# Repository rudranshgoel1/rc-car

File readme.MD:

# Wireless RC Car

### Why did I make it?
bcz i need more hardware projects in my portfolio and also because it seemed like a fun hardware project which was kinda beginner friendly.

### What was the hardest part about this ?
schematic and choosing the pcb art. i really did wake up the creative side of me

Features:

- 4 Arrow Keys for controlling the car
- Arduino Nano for the Main MCU
- L298N Motor Driver
- DC Motors + Wheels
- Custom PCB Art (really cool)
- Custom case

### Fully Built Images

### Working Video

### Schematic

### PCB 

### Case

### 3D view of all parts 

link to full 3d thing-
https://cad.onshape.com/documents/55362c062752c5dd0b9c506b/w/202d1c84392a58531153413c/e/98ba119ae289950db80c791d?renderMode=0&uiState=6a291872275c9443df0429f0

A special thanks to Anay and Shadow who are helping me to make my projects better. Love them so much!

## BOM

[BOM](BOM.csv)

|Name                           |Purpose                            |Quantity|Total Cost (USD)|Link                                        |Distributor    |
|-------------------------------|-----------------------------------|--------|----------------|--------------------------------------------|---------------|
|Arduino Nano                   |Arduino Nano as the MCU            |2       |7.6             |https://www.amazon.in/gp/product/B077TJ8FCF/|Amazon         |
|NRF24L01 Transceiver Module    |Tranceiver module                  |1       |2.5             |https://www.amazon.in/gp/product/B073Q2W112/|Amazon         |
|NRF24L01 Transmitter Module    |Transmitter module                 |1       |2.8             |https://www.amazon.in/gp/product/B0H425R413/|Amazon         |
|Switches for Transmitter       |Switches for controlling the car   |4       |0               |SELF SOURCED                                |SELF SOURCED   |
|Keycaps for the swiches        |Keycaps of the switches            |4       |0               |SELF SOURCED                                |SELF SOURCED   |
|100nF Capacitor                |100nF Capacitor                    |1       |1.3             |https://www.amazon.in/gp/product/B0FCFYSP35/|Amazon         |
|10uF Capacitor                 |10uF Capacitor                     |1       |1.6             |https://www.amazon.in/gp/product/B0GKVJ5FXC/|Amazon         |
|PCB of Transmitter AND Receiver|Main PCBs                          |5 + 5   |16.84           |https://jlcpcb.com/                         |JLPCB          |
|L298N Motor Driver             |Motor which controls the wheels    |1       |2.1             |https://www.amazon.in/gp/product/B00N4KWYDE/|Amazon         |
|DC Motors + Wheels             |DC Motors + Wheels for the car     |1       |4.2             |https://www.amazon.in/gp/product/B07Q22QS3R/|Amazon         |
|Case                           |Shipping - Case for the transmitter|1       |5               |                                            |Printing Legion|
|                               |                                   |        |                |                                            |               |
|                               |                                   |        |43.94           |                                            |               |

Final Price comes out to be 4,185 INR ($43.94)

## Shipping
Amazon = ~$2
Printing Legion = ~$5

Total Shipping = $7

## Total Pricing
The total price comes out to be 4,850 INR ($50.94) [ SHIPPING INCLUDED ]
Total Shipping = $7

The pricing might slightly vary due to flash sales, and dollar market trends.

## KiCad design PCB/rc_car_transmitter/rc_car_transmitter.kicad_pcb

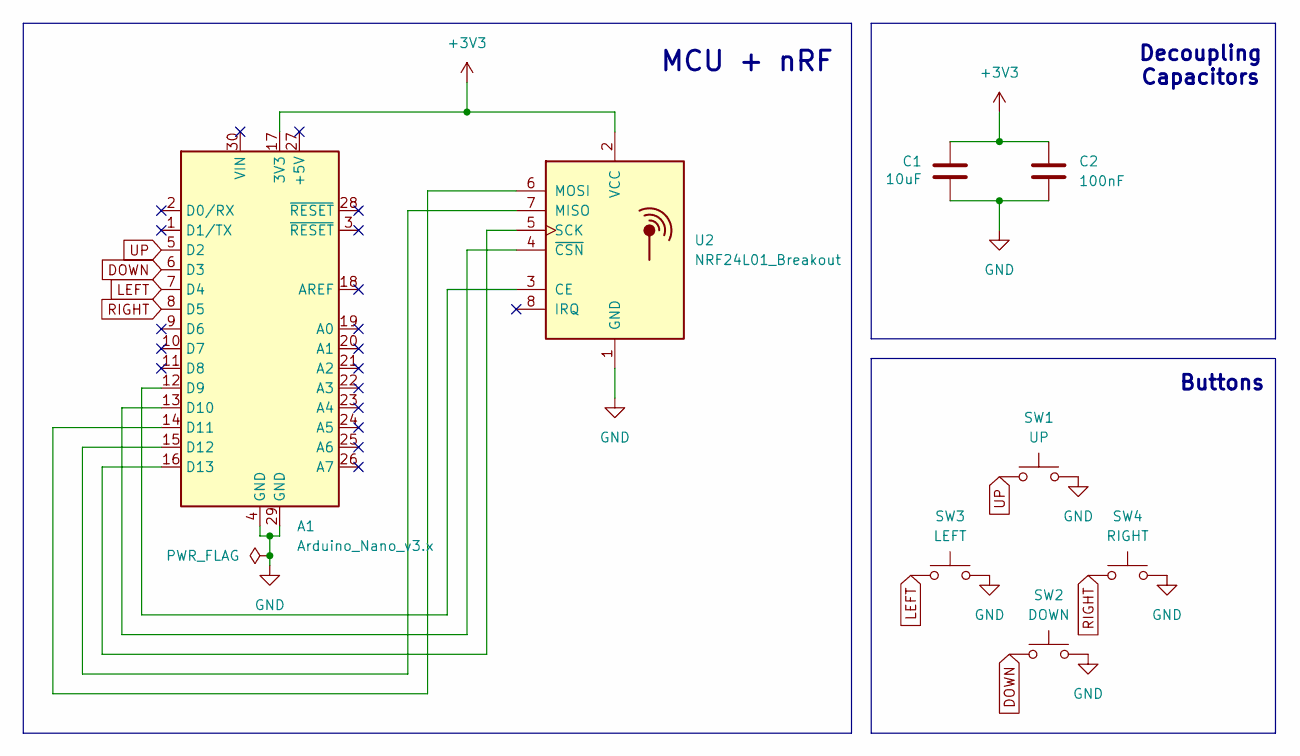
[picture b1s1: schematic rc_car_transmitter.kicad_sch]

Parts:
A1: Arduino_Nano_v3.x; Arduino_Nano
C1: 10uF; CP_Radial_D5.0mm_P2.00mm
C2: 100nF; C_Disc_D5.0mm_W2.5mm_P5.00mm
SW1: UP; SW_Cherry_MX_1.00u_PCB
SW2: DOWN; SW_Cherry_MX_1.00u_PCB
SW3: LEFT; SW_Cherry_MX_1.00u_PCB
SW4: RIGHT; SW_Cherry_MX_1.00u_PCB
U2: NRF24L01_Breakout; nRF24L01_Breakout

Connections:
+3V3: A1.17 (3V3), C1.2, C2.1, U2.2 (VCC)
DOWN: A1.6 (D3), SW2.1
GND: A1.4 (GND), A1.29 (GND), C1.1, C2.2, SW1.2, SW2.2, SW3.2, SW4.2, U2.1 (GND)
LEFT: A1.7 (D4), SW3.1
unnamed: A1.12 (D9), U2.3 (CE)
unnamed: A1.13 (D10), U2.4 (~CSN)
unnamed: A1.14 (D11), U2.6 (MOSI)
unnamed: A1.15 (D12), U2.7 (MISO)
unnamed: A1.16 (D13), U2.5 (SCK)
RIGHT: A1.8 (D5), SW4.1
UP: A1.5 (D2), SW1.1

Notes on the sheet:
MCU + nRF
Decoupling Capacitors
Buttons

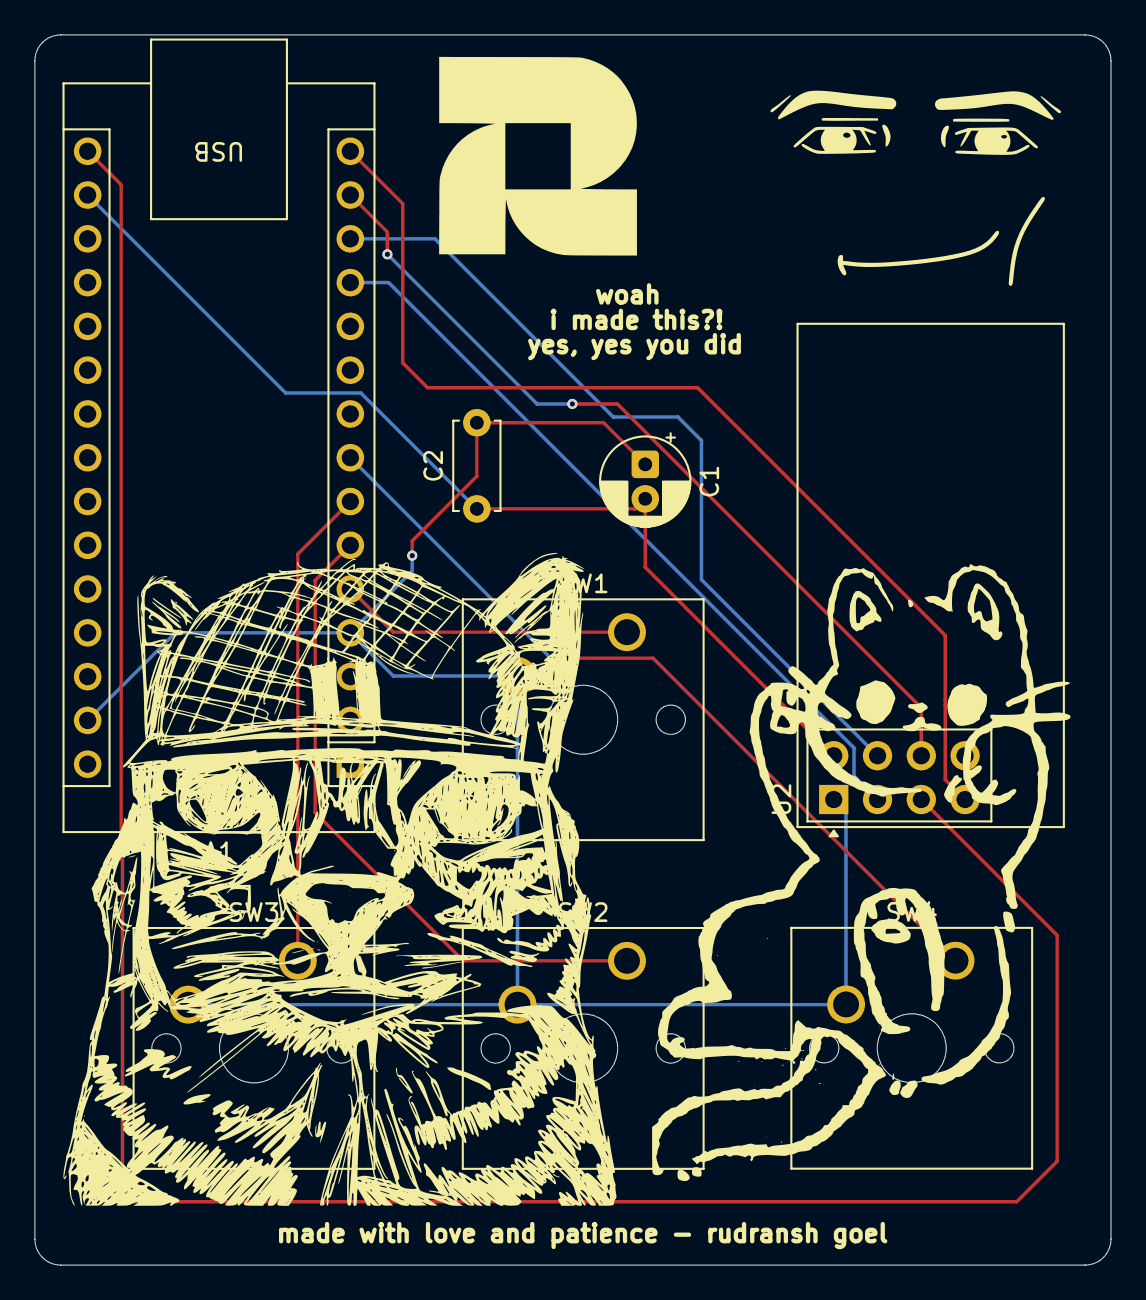
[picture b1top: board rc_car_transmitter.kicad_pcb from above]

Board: 2 copper layers, 62.4 x 71.4 mm, 8 parts (0 on the bottom side), 11 nets.

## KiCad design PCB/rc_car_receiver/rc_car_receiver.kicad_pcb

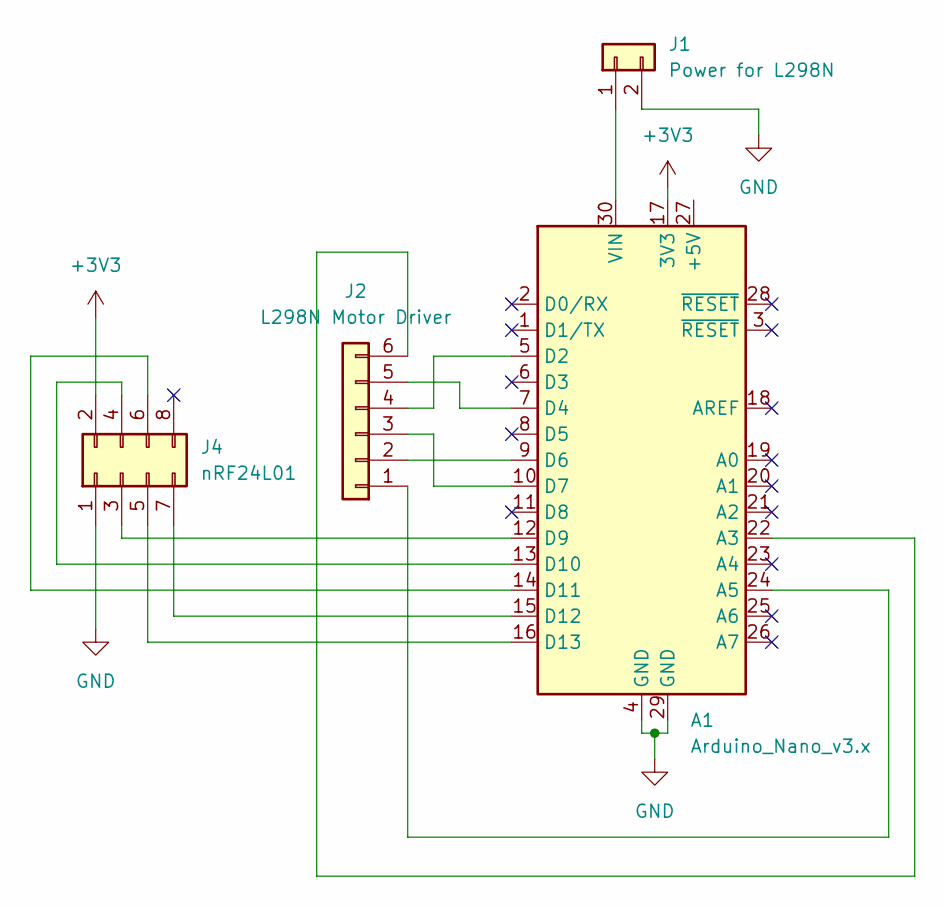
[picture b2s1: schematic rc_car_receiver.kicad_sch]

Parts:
A1: Arduino_Nano_v3.x; Arduino_Nano
J1: Power for L298N; PinHeader_1x02_P2.54mm_Vertical
J2: L298N Motor Driver; PinHeader_1x06_P2.54mm_Vertical
J4: nRF24L01; PinHeader_2x04_P2.54mm_Vertical

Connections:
+3V3: A1.17 (3V3), J4.2
GND: A1.4 (GND), A1.29 (GND), J1.2, J4.1
unnamed: A1.22 (A3), J2.6
unnamed: A1.24 (A5), J2.1
unnamed: A1.5 (D2), J2.4
unnamed: A1.7 (D4), J2.5
unnamed: A1.9 (D6), J2.2
unnamed: A1.10 (D7), J2.3
unnamed: A1.12 (D9), J4.3
unnamed: A1.13 (D10), J4.4
unnamed: A1.14 (D11), J4.6
unnamed: A1.15 (D12), J4.7
unnamed: A1.16 (D13), J4.5
unnamed: A1.30 (VIN), J1.1

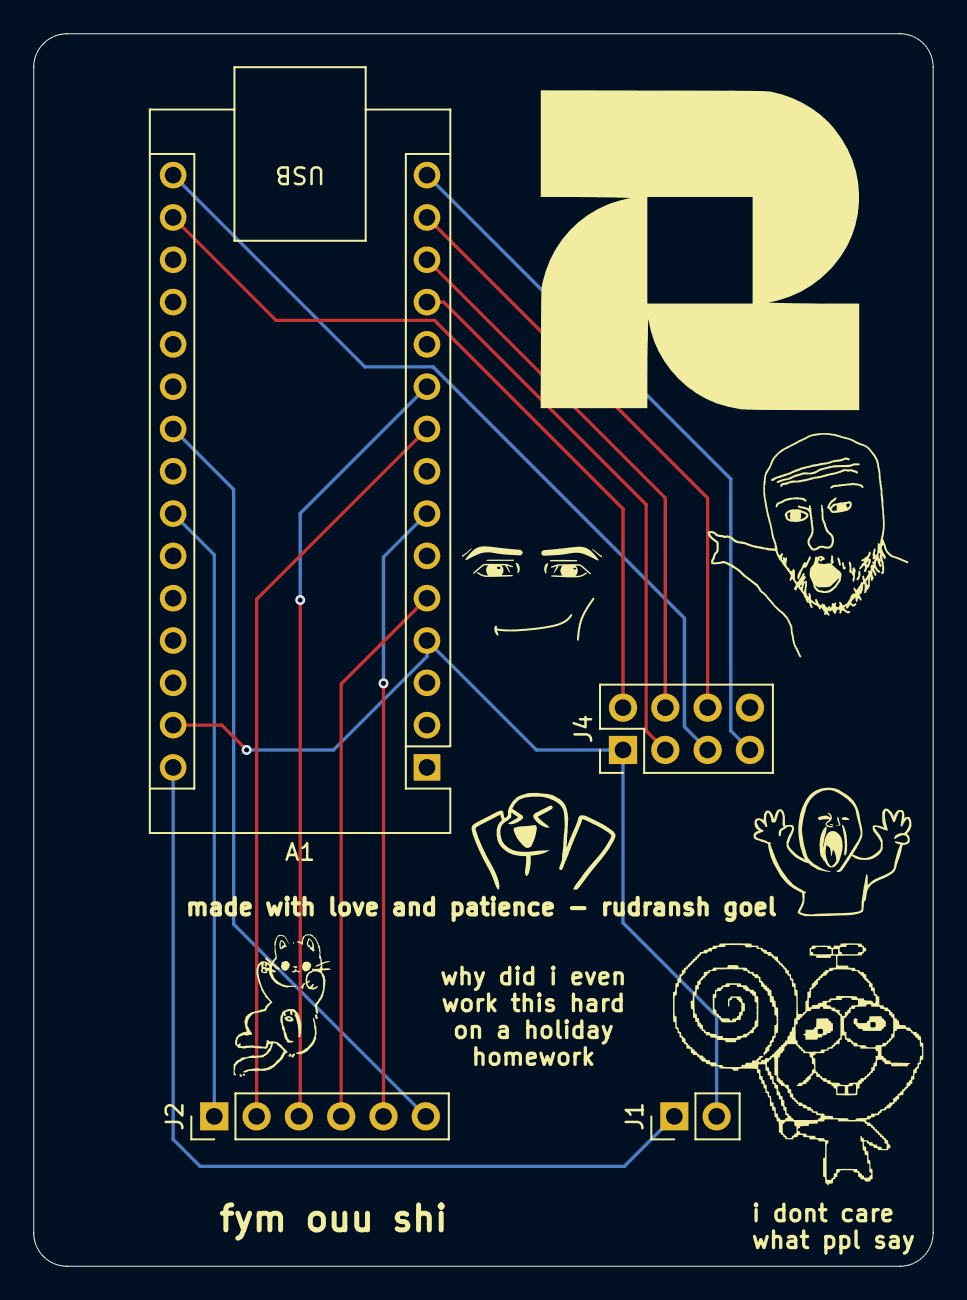
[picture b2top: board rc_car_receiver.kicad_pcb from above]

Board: 2 copper layers, 54.0 x 74.0 mm, 4 parts (0 on the bottom side), 14 nets.

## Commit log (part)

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2026-06-10 main commit
2026-06-10 added firmware and journal.md
2026-06-16 case changes and readme changes
